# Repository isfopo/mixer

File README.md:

# mixer

A small, 4 channel mixer for line-level sources.

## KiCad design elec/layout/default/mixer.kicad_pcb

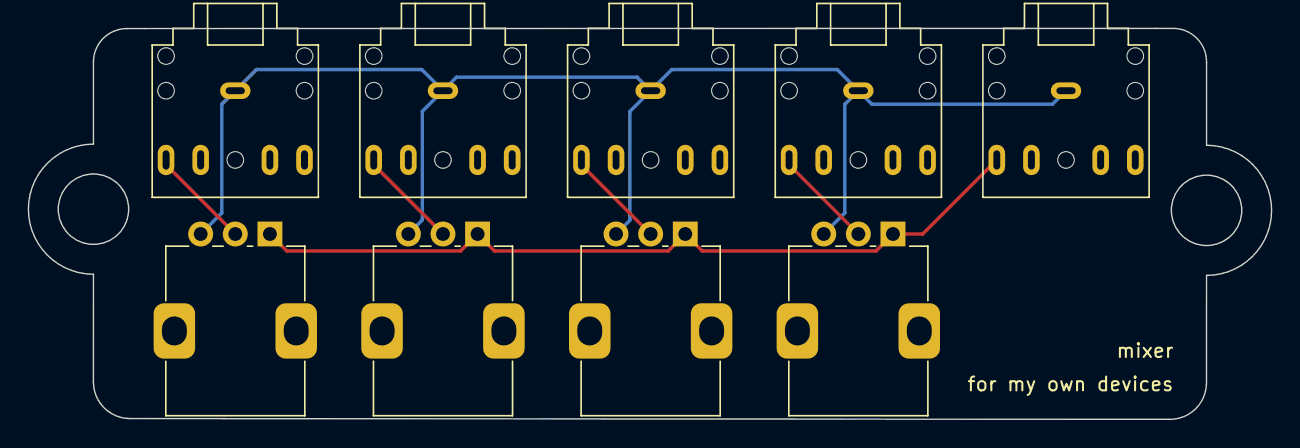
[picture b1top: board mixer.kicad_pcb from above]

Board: 2 copper layers, 89.8 x 28.2 mm, 9 parts (0 on the bottom side), 6 nets.

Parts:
U1, U3, U5, U7, U9: Jack_3.5mm_CUI_SJ1-3525N_Horizontal
U2, U4, U6, U8: Potentiometer_Alps_RK09K_Single_Vertical

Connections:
ground: U1.S, U2.3, U3.S, U4.3, U5.S, U6.3, U7.S, U8.3, U9.S
in_1.in-t: U1.T, U2.2
in_2.in-t: U3.T, U4.2
in_3.in-t: U5.T, U6.2
in_4.in-t: U7.T, U8.2
output: U2.1, U4.1, U6.1, U8.1, U9.T

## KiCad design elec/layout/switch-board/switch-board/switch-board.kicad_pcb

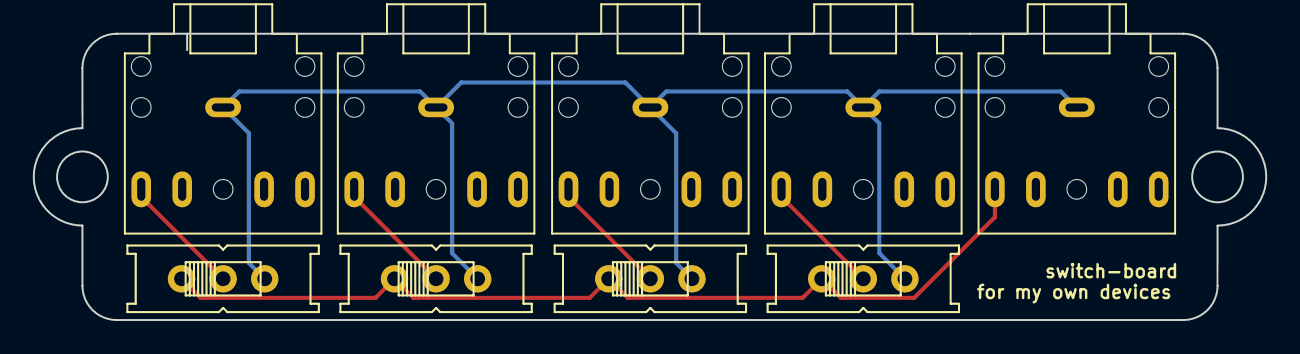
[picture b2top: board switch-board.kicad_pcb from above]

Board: 2 copper layers, 75.2 x 17.5 mm, 9 parts (0 on the bottom side), 6 nets.

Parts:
U1, U3, U5, U7, U9: Jack_3.5mm_CUI_SJ1-3525N_Horizontal
U2, U4, U6, U8: EG1218

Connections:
ground: U1.S, U2.S, U3.S, U4.S, U5.S, U6.S, U7.S, U8.S, U9.S
in_1.in-t: U1.T, U2.P
in_2.in-t: U3.T, U4.P
in_3.in-t: U5.T, U6.P
in_4.in-t: U7.T, U8.P
output: U2.O, U4.O, U6.O, U8.O, U9.T

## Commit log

2024-04-27 creates mixer
2024-04-28 creates switch board
2024-05-04 adds 3d printed base
